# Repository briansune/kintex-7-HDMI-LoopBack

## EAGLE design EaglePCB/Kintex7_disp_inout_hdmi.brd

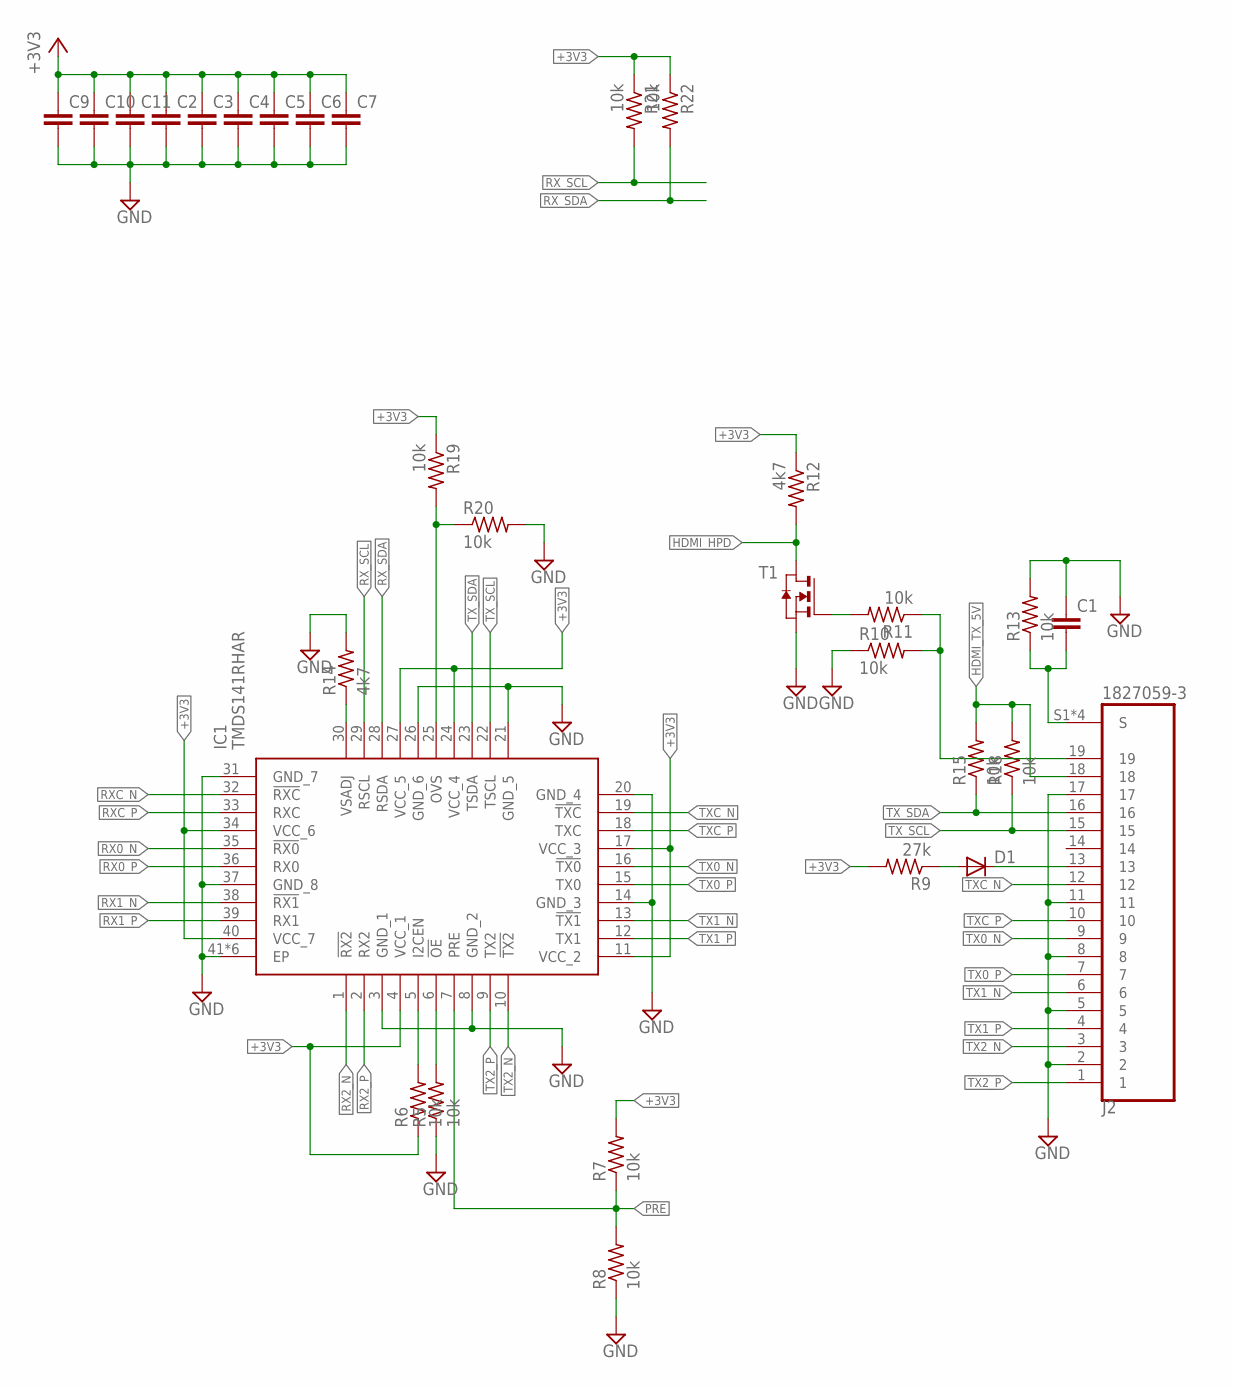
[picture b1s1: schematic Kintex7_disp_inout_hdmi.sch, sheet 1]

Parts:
C1, C2, C3, C4, C5, C6, C7, C9, C10, C11: C-EUC0603; C0603
D1: DIODE-MINIMELF; MINIMELF
IC1: TMDS141RHAR; QFN50P600X600X100-41N
J2: 1827059-3; TE_1827059-3
R5, R6, R7, R8, R10, R11, R13, R15, R18, R19, R20, R21, R22: 10k; R0805
R9: 27k; R0805
R12, R14: 4k7; R0805
T1: NMOSSOT23; SOT-23

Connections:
+3V3: C2.1, C3.1, C4.1, C5.1, C6.1, C7.1, C9.1, C10.1, C11.1, IC1.4 (VCC_1), IC1.11 (VCC_2), IC1.17 (VCC_3), IC1.24 (VCC_4), IC1.27 (VCC_5), IC1.34 (VCC_6), IC1.40 (VCC_7), R6.1, R7.2, R9.2, R12.1, R19.1, R21.1, R22.1; also elsewhere on the board
GND: C1.1, C2.2, C3.2, C4.2, C5.2, C6.2, C7.2, C9.2, C10.2, C11.2, IC1.3 (GND_1), IC1.8 (GND_2), IC1.14 (GND_3), IC1.20 (GND_4), IC1.21 (GND_5), IC1.26 (GND_6), IC1.31 (GND_7), IC1.37 (GND_8), IC1.41 (EP), IC1.P$1 (EP), IC1.P$2 (EP), IC1.P$3 (EP), IC1.P$4 (EP), IC1.P$5 (EP), J2.2, J2.5, J2.8, J2.11, J2.17, R5.1, R8.1, R10.1, R13.2, R14.2, R20.2, T1.2 (S); also elsewhere on the board
HDMI_HPD: R12.2, T1.1 (D); also elsewhere on the board
HDMI_TX_5V: J2.18, R15.2, R18.2
unnamed: D1.A, R9.1
unnamed: IC1.6 (!OE), R5.2
unnamed: IC1.5 (I2CEN), R6.2
unnamed: D1.C, J2.13
unnamed: IC1.25 (OVS), R19.2, R20.1
unnamed: R11.2, T1.3 (G)
unnamed: C1.2, J2.S1 (S), J2.S2 (S), J2.S3 (S), J2.S4 (S), R13.1
unnamed: IC1.30 (VSADJ), R14.1
unnamed: J2.19, R10.2, R11.1
PRE: IC1.7 (PRE), R7.1, R8.2
RX0_N: IC1.35 (!RX0); also elsewhere on the board
RX0_P: IC1.36 (RX0); also elsewhere on the board
RX1_N: IC1.38 (!RX1); also elsewhere on the board
RX1_P: IC1.39 (RX1); also elsewhere on the board
RX2_N: IC1.1 (!RX2); also elsewhere on the board
RX2_P: IC1.2 (RX2); also elsewhere on the board
RXC_N: IC1.32 (!RXC); also elsewhere on the board
RXC_P: IC1.33 (RXC); also elsewhere on the board
RX_SCL: IC1.29 (RSCL), R21.2; also elsewhere on the board
RX_SDA: IC1.28 (RSDA), R22.2; also elsewhere on the board
TX0_N: IC1.16 (!TX0), J2.9
TX0_P: IC1.15 (TX0), J2.7
TX1_N: IC1.13 (!TX1), J2.6
TX1_P: IC1.12 (TX1), J2.4
TX2_N: IC1.10 (!TX2), J2.3
TX2_P: IC1.9 (TX2), J2.1
TXC_N: IC1.19 (!TXC), J2.12
TXC_P: IC1.18 (TXC), J2.10
TX_SCL: IC1.22 (TSCL), J2.15, R18.1
TX_SDA: IC1.23 (TSDA), J2.16, R15.1

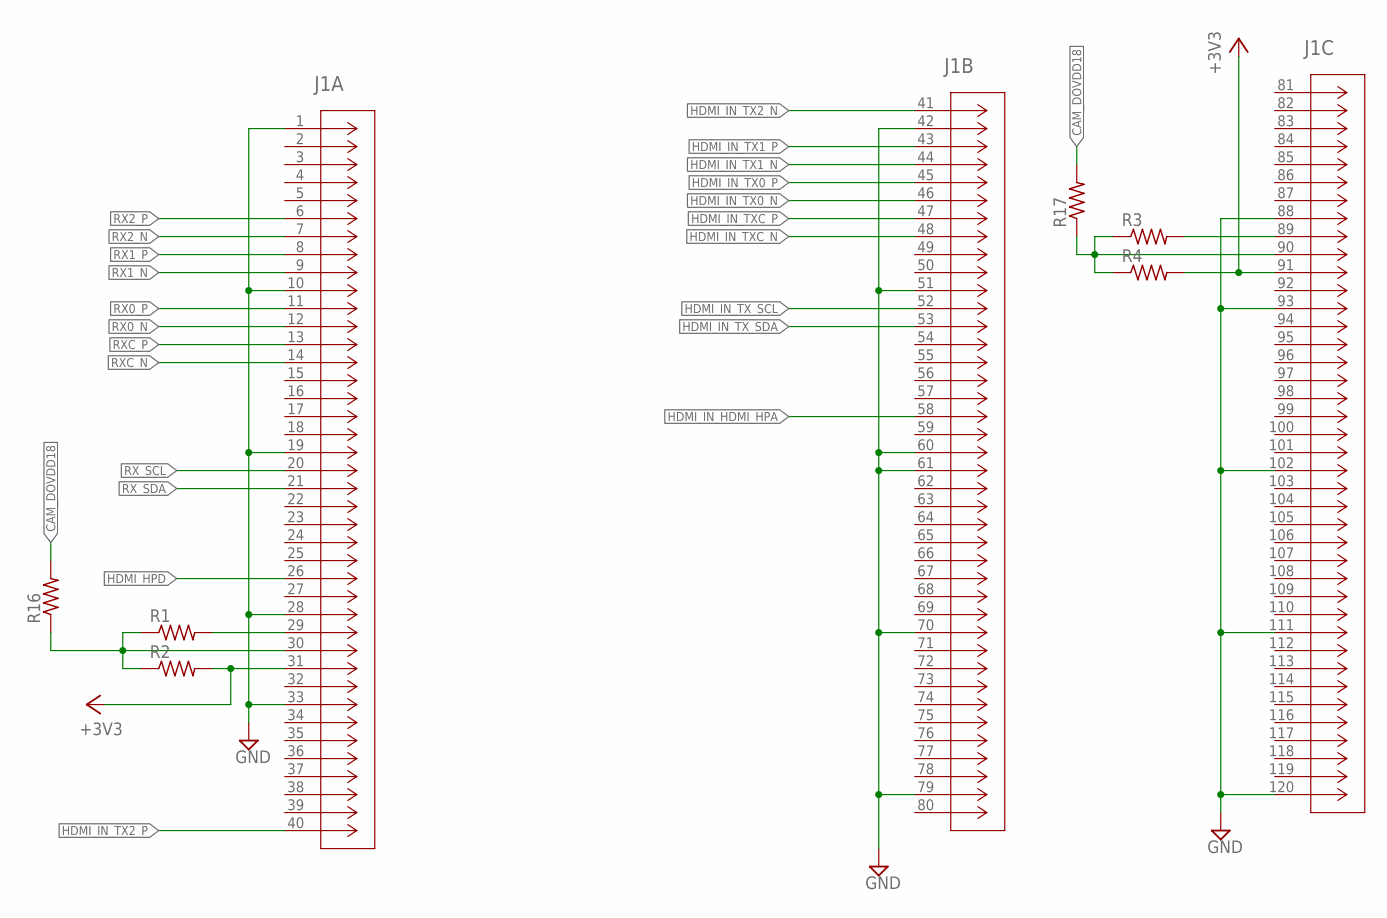
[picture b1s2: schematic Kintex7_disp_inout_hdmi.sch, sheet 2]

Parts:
J1: 5177985-5; CONN_5177985-5
R1, R2, R3, R4, R16, R17: R-US_R0805; R0805

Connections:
+3V3: J1.31, J1.91, R2.2, R4.2; also elsewhere on the board
CAM_DOVDD18: R16.2, R17.2
GND: J1.1, J1.10, J1.19, J1.28, J1.33, J1.42, J1.51, J1.60, J1.61, J1.70, J1.79, J1.88, J1.93, J1.102, J1.111, J1.120; also elsewhere on the board
HDMI_HPD: J1.26; also elsewhere on the board
HDMI_IN_HDMI_HPA: J1.58; also elsewhere on the board
HDMI_IN_TX0_N: J1.46; also elsewhere on the board
HDMI_IN_TX0_P: J1.45; also elsewhere on the board
HDMI_IN_TX1_N: J1.44; also elsewhere on the board
HDMI_IN_TX1_P: J1.43; also elsewhere on the board
HDMI_IN_TX2_N: J1.41; also elsewhere on the board
HDMI_IN_TX2_P: J1.40; also elsewhere on the board
HDMI_IN_TXC_N: J1.48; also elsewhere on the board
HDMI_IN_TXC_P: J1.47; also elsewhere on the board
HDMI_IN_TX_SCL: J1.52; also elsewhere on the board
HDMI_IN_TX_SDA: J1.53; also elsewhere on the board
unnamed: J1.90, R3.1, R4.1, R17.1
unnamed: J1.29, R1.2
unnamed: J1.89, R3.2
unnamed: J1.30, R1.1, R2.1, R16.1
RX0_N: J1.12; also elsewhere on the board
RX0_P: J1.11; also elsewhere on the board
RX1_N: J1.9; also elsewhere on the board
RX1_P: J1.8; also elsewhere on the board
RX2_N: J1.7; also elsewhere on the board
RX2_P: J1.6; also elsewhere on the board
RXC_N: J1.14; also elsewhere on the board
RXC_P: J1.13; also elsewhere on the board
RX_SCL: J1.20; also elsewhere on the board
RX_SDA: J1.21; also elsewhere on the board

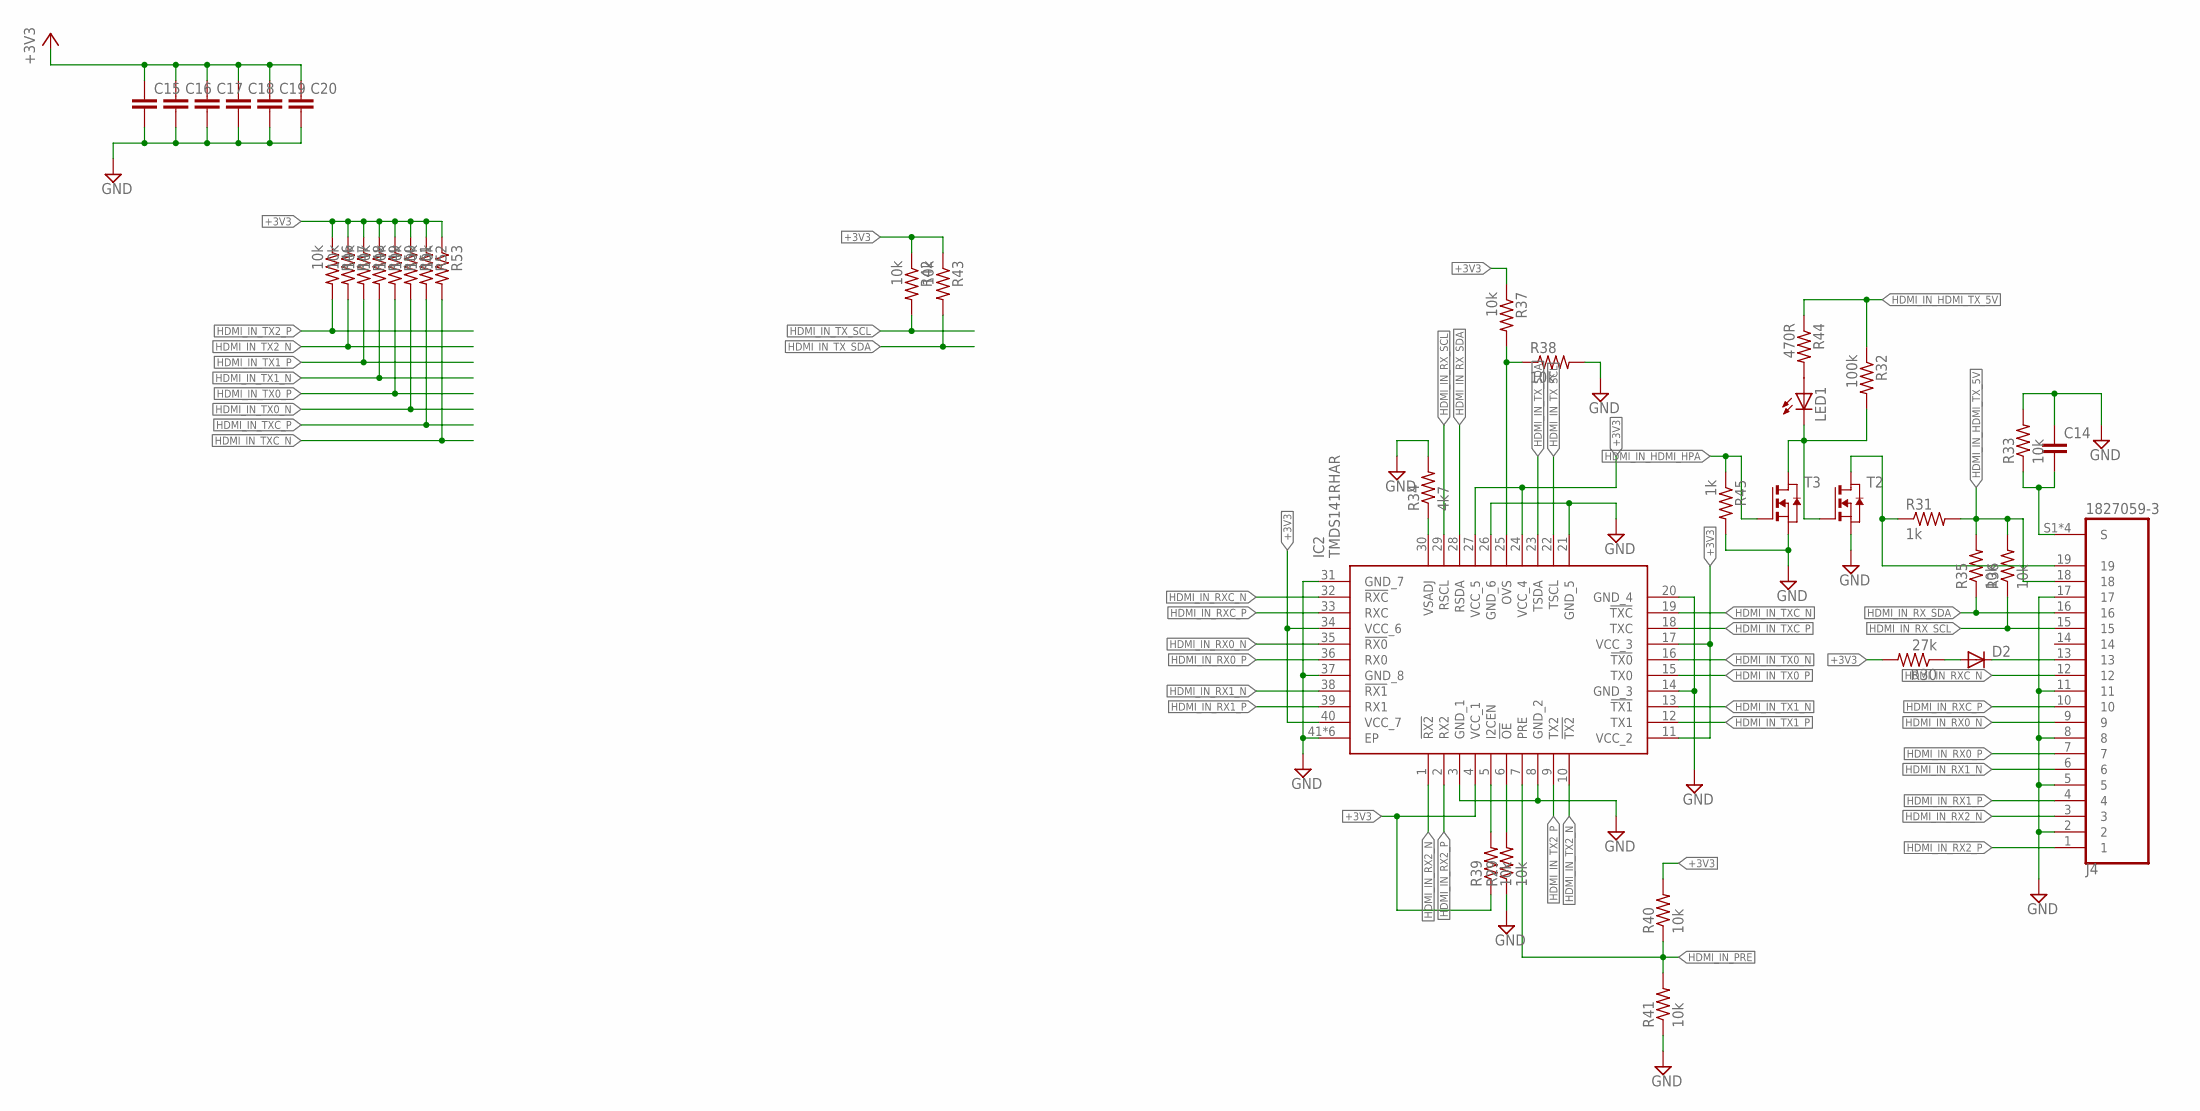
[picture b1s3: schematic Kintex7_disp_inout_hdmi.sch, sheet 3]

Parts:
C14, C15, C16, C17, C18, C19, C20: C-EUC0603; C0603
D2: DIODE-MINIMELF; MINIMELF
IC2: TMDS141RHAR; QFN50P600X600X100-41N
J4: 1827059-3; TE_1827059-3
LED1: LEDCHIPLED_0603; CHIPLED_0603
R29, R33, R35, R36, R37, R38, R39, R40, R41, R42, R43, R46, R47, R48, R49, R50, R51, R52, R53: 10k; R0805
R30: 27k; R0805
R31, R45: 1k; R0805
R32: 100k; R0805
R34: 4k7; R0805
R44: 470R; R0805
T2, T3: NMOSSOT23; SOT-23

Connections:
+3V3: C15.1, C16.1, C17.1, C18.1, C19.1, C20.1, IC2.4 (VCC_1), IC2.11 (VCC_2), IC2.17 (VCC_3), IC2.24 (VCC_4), IC2.27 (VCC_5), IC2.34 (VCC_6), IC2.40 (VCC_7), R30.2, R37.1, R39.1, R40.2, R42.1, R43.1, R46.1, R47.1, R48.1, R49.1, R50.1, R51.1, R52.1, R53.1; also elsewhere on the board
GND: C14.1, C15.2, C16.2, C17.2, C18.2, C19.2, C20.2, IC2.3 (GND_1), IC2.8 (GND_2), IC2.14 (GND_3), IC2.20 (GND_4), IC2.21 (GND_5), IC2.26 (GND_6), IC2.31 (GND_7), IC2.37 (GND_8), IC2.41 (EP), IC2.P$1 (EP), IC2.P$2 (EP), IC2.P$3 (EP), IC2.P$4 (EP), IC2.P$5 (EP), J4.2, J4.5, J4.8, J4.11, J4.17, R29.1, R33.2, R34.2, R38.2, R41.1, R45.2, T2.2 (S), T3.2 (S); also elsewhere on the board
HDMI_IN_HDMI_HPA: R45.1, T3.3 (G); also elsewhere on the board
HDMI_IN_HDMI_TX_5V: J4.18, R31.2, R32.1, R35.2, R36.2, R44.1
HDMI_IN_PRE: IC2.7 (PRE), R40.1, R41.2
HDMI_IN_RX0_N: IC2.35 (!RX0), J4.9
HDMI_IN_RX0_P: IC2.36 (RX0), J4.7
HDMI_IN_RX1_N: IC2.38 (!RX1), J4.6
HDMI_IN_RX1_P: IC2.39 (RX1), J4.4
HDMI_IN_RX2_N: IC2.1 (!RX2), J4.3
HDMI_IN_RX2_P: IC2.2 (RX2), J4.1
HDMI_IN_RXC_N: IC2.32 (!RXC), J4.12
HDMI_IN_RXC_P: IC2.33 (RXC), J4.10
HDMI_IN_RX_SCL: IC2.29 (RSCL), J4.15, R36.1
HDMI_IN_RX_SDA: IC2.28 (RSDA), J4.16, R35.1
HDMI_IN_TX0_N: IC2.16 (!TX0), R51.2; also elsewhere on the board
HDMI_IN_TX0_P: IC2.15 (TX0), R50.2; also elsewhere on the board
HDMI_IN_TX1_N: IC2.13 (!TX1), R49.2; also elsewhere on the board
HDMI_IN_TX1_P: IC2.12 (TX1), R48.2; also elsewhere on the board
HDMI_IN_TX2_N: IC2.10 (!TX2), R47.2; also elsewhere on the board
HDMI_IN_TX2_P: IC2.9 (TX2), R46.2; also elsewhere on the board
HDMI_IN_TXC_N: IC2.19 (!TXC), R53.2; also elsewhere on the board
HDMI_IN_TXC_P: IC2.18 (TXC), R52.2; also elsewhere on the board
HDMI_IN_TX_SCL: IC2.22 (TSCL), R42.2; also elsewhere on the board
HDMI_IN_TX_SDA: IC2.23 (TSDA), R43.2; also elsewhere on the board
unnamed: IC2.6 (!OE), R29.2
unnamed: D2.A, R30.1
unnamed: D2.C, J4.13
unnamed: C14.2, J4.S1 (S), J4.S2 (S), J4.S3 (S), J4.S4 (S), R33.1
unnamed: IC2.30 (VSADJ), R34.1
unnamed: J4.19, R31.1, T2.1 (D)
unnamed: IC2.25 (OVS), R37.2, R38.1
unnamed: IC2.5 (I2CEN), R39.2
unnamed: LED1.C, R32.2, T2.3 (G), T3.1 (D)
unnamed: LED1.A, R44.2

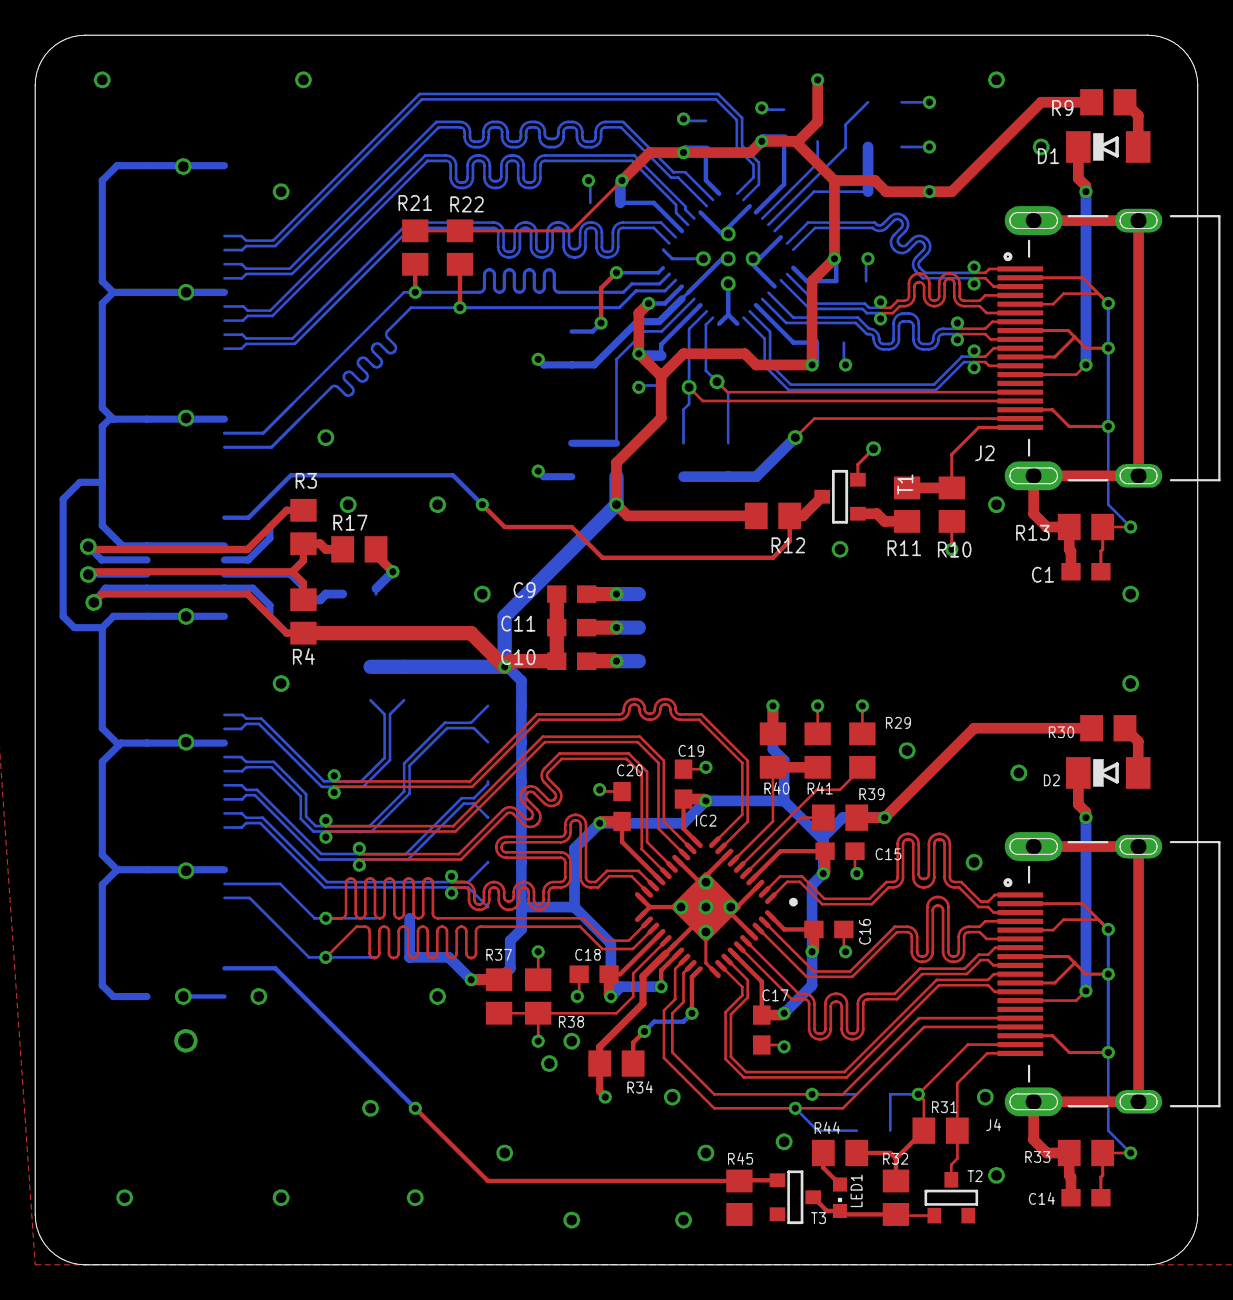
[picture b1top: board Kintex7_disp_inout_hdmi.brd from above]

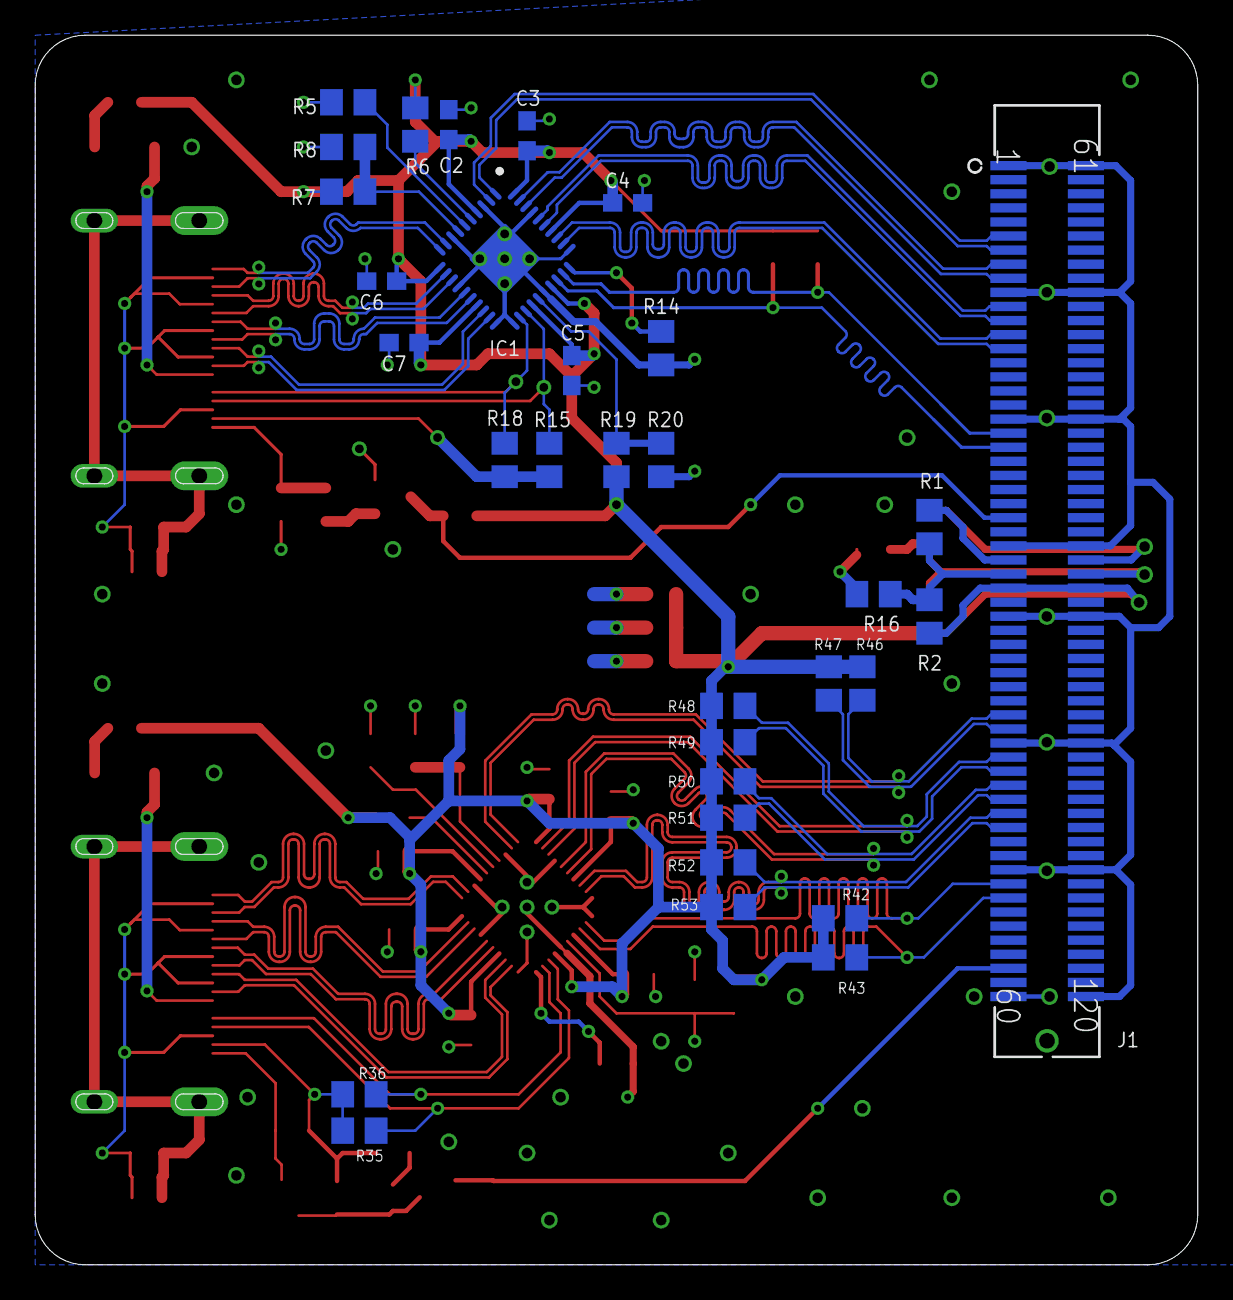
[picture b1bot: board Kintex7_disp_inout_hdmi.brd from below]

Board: 2 copper layers, 66.0 x 69.8 mm, 75 parts (32 on the bottom side), 72 nets.

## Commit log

2020-05-13 Kintex-7 HDMI LoopBack
